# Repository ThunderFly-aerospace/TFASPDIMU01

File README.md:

# TFASPDIMU01 - sdp3x differental pressure sensor and IMU 9-axis unit

ThunderFly TFASPDIMU01 is SPI/I2C sensor board equipped with a differential pressure sensor (Senserion [SDP3x](https://www.sensirion.com/sdp3x/)) and 9-axis motion tracking sensor ([ICM-20948](https://invensense.tdk.com/products/motion-tracking/9-axis/icm-20948/)). Board is equipped with 7pin JST-GH connector. The sensor board is designed for multiple uses. It can be used as a self-adjusting anemometer [WINDGAUGE03](https://github.com/mlab-modules/WINDGAUGE03) or as an airspeed sensor for UAVs with optional function as the external magnetometer.

TFASPDIMU is commercially available from [ThunderFly s.r.o.](https://www.thunderfly.cz/), write an email to info@thunderfly.cz or shop at [Tindie store](https://www.tindie.com/stores/thunderfly/).

## Specification
 * Type: Differential and 9-axis motion sensor board
 * Mass: 3 g
 * Size: 36 x 14 mm
 * Power: +5 V
 * Connection: 7pin JST-GH connector, custom pinout

**SDP3x**
 * Range: +/- 125/500 Pa (depending on exact sensor type)
 * Excellent accuracy and repeatability, even below one Pascal
 * No zero-point offset, no temperature drift
 * Calibrated and temperature compensated
 * Fast sampling time of 2kHz at 16 bit resolution
 * I2C address: 0x21 (d33)

 **ICM-20948**
 * 3-axis gyroscope, 3-axis accelerometer, 3-axis compass (magnetometer)
 * Onboard Digital Motion Processor (DMP)
 * On-Chip 16-bit ADCs and Programmable Filters
 * 7 MHz SPI or 400 kHz Fast Mode I²C
 * Digital temperature sensor
 * Default I2C address: 0x68 (0d104), can be changed to 0x69 (0d105) by moving the resistor R2->R1. 

## Example of uses

### WINDGUAGE01

Ground control station anemometer [WINDGAUGE03](https://github.com/mlab-modules/WINDGAUGE03)

### TFSLOT01 - UAV airspeed sensor

Our [TFSLOT](https://github.com/ThunderFly-aerospace/TFSLOT01) senzor is an airspeed sensor for use mainly on UAV. Due to 3D printed case it is possible to optimalize part according to the location of sensor on UAV and tune their characteristics. First use of this sensor was on our autogyro [TF-G2](https://github.com/ThunderFly-aerospace/TF-G2/).

More details about this solution is available in the repository [TFSLOT01](https://github.com/ThunderFly-aerospace/TFSLOT01).

### TFPIPE01 - UAV airspeed sensor

Symmetric variant of TFSLOT sensor for different mounting options [TFPIPE01](https://github.com/ThunderFly-aerospace/TFPIPE01).

### TFVENTUFO - omnidirectional anemometer
This anemometer should also based on venturi effect. Thanks to an clever design, it will measure the wind speed from all directions (without knowing the direction).

### Angle of Attack sensor

In case of mounting on rotation slip-ring bearing the sensor could sense air [AoA of the vehicle](https://en.wikipedia.org/wiki/Angle_of_attack). Due to ability to turn in direction of airflow. The turnig direction could be sensed differentialy to position of aircraft by IMU embedded in the TFASPDIMU01 sensor. 

## Hardware

### Eletronic schema

Full schema is avialible in [PDF](/hw/sch_pcb/TFASPDIMU01.pdf)

### Hardware layout

** IMG - technical draft **

### Pinout
|Pin #| I2C | SPI  |
| --- |:---:|:----:|
| 1   | +5V | +5V  |
| 2   | SCL | SCK  |
| 3   | --  | MISO |
| 4   | SDA | MOSI |
| 5   | --  | CS   |
| 6   | INT | INT  |
| 7   | GND | GND  |
> Due to the possible wider use of the sensor, a standard pixhawk pinout is not used.

#### PixHawk autopilot cable

To increase the transmission quality, it is recommended to create pairs SDA,GND and SCL,+5V on the cable (as shown in image)

| TFASPDIMU01 Pin | Sigal | Pixhawk | Color |
| ---------------:|:-----:|:-------:|-------|
|   1             | +5V   |  1      | Red   |
|   2             | SCL   |  2      | Yellow|
|   4             | SDA   |  3      | Green |
|   7             | GND   |  4      | Black |
> Pixhawk pinout is listed according to the [Pixhawk connector standard](https://github.com/pixhawk/Pixhawk-Standards/blob/master/DS-009%20Pixhawk%20Connector%20Standard.pdf).

## Usage

### Python
For reading data from the sensor, we have prepared a python script in PyMLAB library that uses the pySMBus to readout data. It can be used directly from a computer with a corresponding converter (for example MLAB [USBI2C01A](https://wiki.mlab.cz/doku.php?id=cs:usbi2c)) or with one-board computers (Odroid, raspberry and similar) that have own smbus output.

#### Calibration vertification
Calibration can be verified by mounting of an anemometer to car roof and comparing it to speed obtained from GPS (gpsd). This needs to be done in windless weather.

### PX4
> We are now working on implementation of driver into PX4 stack.

Main usage of this sensor is as airspeed sensor. It can be also used as an external magnetometer and thermometer.

### Ardupilot
We are currently unable to implement the sensor in the Ardupilot flight stack. However, we will be happy to provide assistance with implementation. You can [contact us](https://www.thunderfly.cz/contact-us.html)

#### configuration
*TODO*

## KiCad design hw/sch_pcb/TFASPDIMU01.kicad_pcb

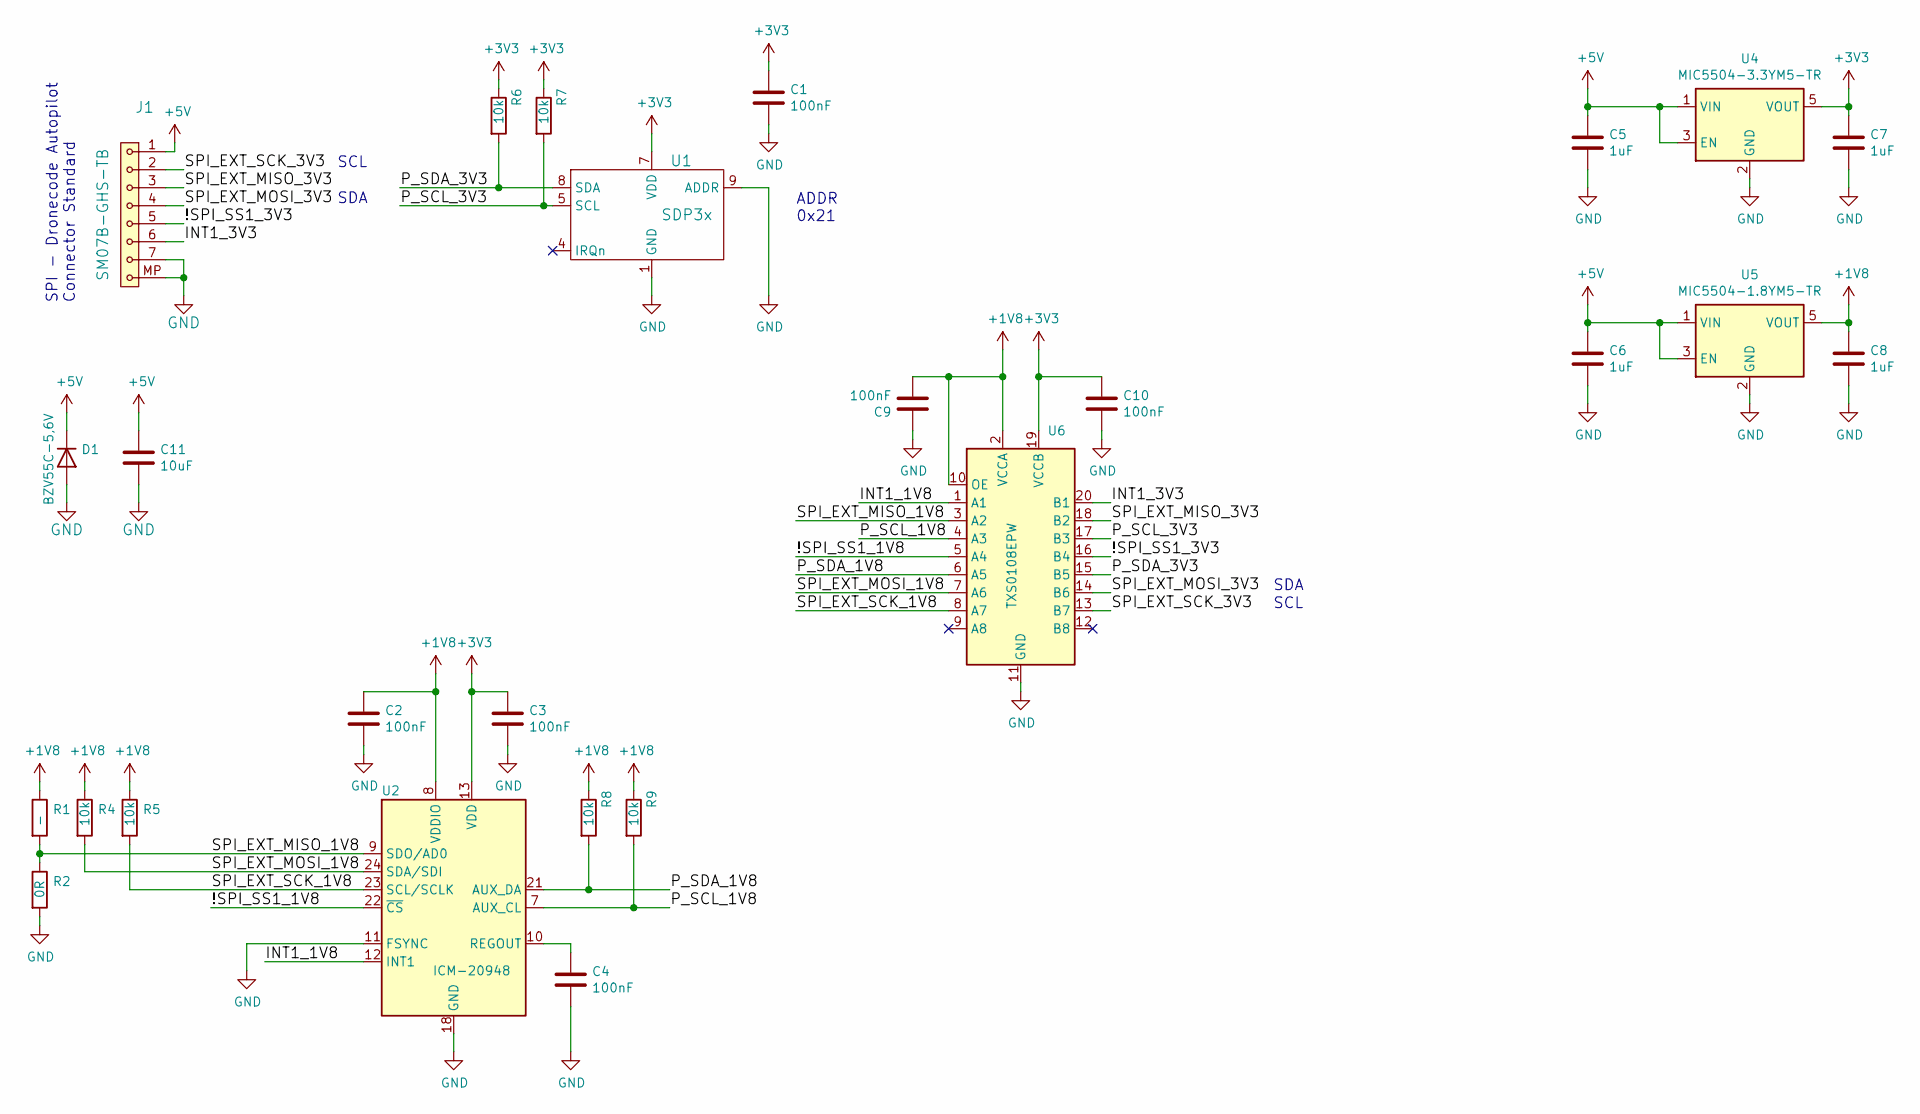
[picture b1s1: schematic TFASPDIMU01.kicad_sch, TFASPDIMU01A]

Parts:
C1, C2, C3, C4, C9, C10: 100nF; SMD-0603
C5, C6, C7, C8: 1uF; SMD-0603
C11: 10uF; SMD-0805
D1: BZV55C-5,6V; D_MiniMELF
J1: SM07B-GHS-TB; JST_GH_SM07B-GHS-TB_1x07-1MP_P1.25mm_Horizontal
R1: -; SMD-0603
R2: 0R; SMD-0603
R4, R5, R6, R7, R8, R9: 10k; SMD-0603
U1: SDP3x
U2: ICM-20948; InvenSense_QFN-24_3x3mm_P0.4mm
U4: MIC5504-3.3YM5-TR; SOT-23-5
U5: MIC5504-1.8YM5-TR; SOT-23-5
U6: TXS0108EPW; TSSOP-20_4.4x6.5mm_P0.65mm

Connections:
+1V8: C2.1, C8.1, C9.2, R1.1, R4.1, R5.1, R8.1, R9.1, U2.8 (VDDIO), U5.5 (VOUT), U6.2 (VCCA), U6.10 (OE)
+3V3: C1.1, C3.1, C7.1, C10.1, R6.1, R7.1, U1.7 (VDD), U2.13 (VDD), U4.5 (VOUT), U6.19 (VCCB)
+5V: C5.1, C6.1, C11.1, D1.1 (K), J1.1, U4.1 (VIN), U4.3 (EN), U5.1 (VIN), U5.3 (EN)
/!SPI_SS1_1V8: U2.22 (~CS), U6.5 (A4)
/!SPI_SS1_3V3: J1.5, U6.16 (B4)
/INT1_1V8: U2.12 (INT1), U6.1 (A1)
/INT1_3V3: J1.6, U6.20 (B1)
/P_SCL_1V8: R9.2, U2.7 (AUX_CL), U6.4 (A3)
/P_SCL_3V3: R7.2, U1.5 (SCL), U6.17 (B3)
/P_SDA_1V8: R8.2, U2.21 (AUX_DA), U6.6 (A5)
/P_SDA_3V3: R6.2, U1.8 (SDA), U6.15 (B5)
/SPI_EXT_MISO_1V8: R1.2, R2.1, U2.9 (SDO/AD0), U6.3 (A2)
/SPI_EXT_MISO_3V3: J1.3, U6.18 (B2)
/SPI_EXT_MOSI_1V8: R4.2, U2.24 (SDA/SDI), U6.7 (A6)
/SPI_EXT_MOSI_3V3: J1.4, U6.14 (B6)
/SPI_EXT_SCK_1V8: R5.2, U2.23 (SCL/SCLK), U6.8 (A7)
/SPI_EXT_SCK_3V3: J1.2, U6.13 (B7)
GND: C1.2, C2.2, C3.2, C4.2, C5.2, C6.2, C7.2, C8.2, C9.1, C10.2, C11.2, D1.2 (A), J1.7, J1.MP, R2.2, U1.1 (GND), U1.2 (GND), U1.3 (GND), U1.6 (GND), U1.9 (ADDR), U1.10 (GND), U1.11 (GND), U1.17 (GND), U1.18 (GND), U2.11 (FSYNC), U2.18 (GND), U2.20 (GND), U4.2 (GND), U5.2 (GND), U6.11 (GND)
unnamed: C4.1, U2.10 (REGOUT)

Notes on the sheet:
SDA
SCL
ADDR 0x21
SPI - Dronecode Autopilot Connector Standard

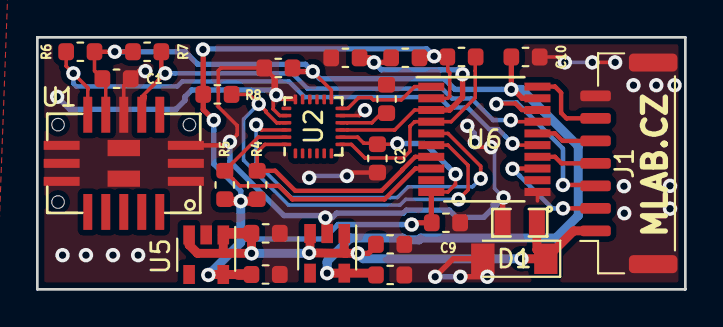
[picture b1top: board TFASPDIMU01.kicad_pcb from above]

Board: 2 copper layers, 36.0 x 14.0 mm, 26 parts (0 on the bottom side), 19 nets.

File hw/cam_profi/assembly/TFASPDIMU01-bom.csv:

Component,Description,Part,References,Value,Footprint,Quantity Per PCB,Datasheet,ust_id
1,Unpolarized capacitor,C,C1C2C3C4C9C10,100nF,SMD-0603,6,~,5c70984712875079b91f8b4c
2,Unpolarized capacitor,C,C5C6C7C8,1uF,SMD-0603,4,~,5c70984712875079b91f8b50
3,Unpolarized capacitor,C,C11,10uF,SMD-0805,1,~,5c70984812875079b91f8bbd
4,Diode,D,D1,"BZV55C-5,6V",D_MiniMELF,1,~,5c70984512875079b91f88b1
5,1x08 2.54 mm pitch header,SM07B-GHS-TB,J1,SM07B-GHS-TB,JST_GH_SM07B-GHS-TB_1x07-1MP_P1.25mm_Horizontal,1,,5c7250081287500b4e112e78
6,Resistor,R,R2,0R,SMD-0603,1,~,5c70984512875079b91f896b
7,Resistor,R,R4R5R6R7R8R9,10k,SMD-0603,6,~,5c70984612875079b91f899f
8,Resistor,R,R1,-,SMD-0603,1,~,
9,"InvenSense 9-Axis Motion Sensor, Accelerometer, Gyroscope, Compass, I2C/SPI, QFN-24",ICM-20948,U2,ICM-20948,InvenSense_QFN-24_3x3mm_P0.4mm,1,http://www.invensense.com/wp-content/uploads/2016/06/DS-0001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,5c725a431287500b4e112ef5
10,"300mA Low-dropout Voltage Regulator, Vout 1.8V, Vin up to 5.5V, SOT-23",MIC5504-1.8YM5,U5,MIC5504-1.8YM5-TR,SOT-23-5,1,http://ww1.microchip.com/downloads/en/DeviceDoc/MIC550X.pdf,5c7256781287500b4e112eba
11,"300mA Low-dropout Voltage Regulator, Vout 3.3V, Vin up to 5.5V, SOT-23",MIC5504-3.3YM5,U4,MIC5504-3.3YM5-TR,SOT-23-5,1,http://ww1.microchip.com/downloads/en/DeviceDoc/MIC550X.pdf,5c7255e81287500b4e112ea2
12,,SDP3x,U1,SDP3x,SDP3x,1,,5c70984812875079b91f8bd0
13,"Bidirectional  level-shifting voltage translator, TSSOP-20",TXS0108EPW,U6,TXS0108EPW,TSSOP-20_4.4x6.5mm_P0.65mm,1,www.ti.com/lit/ds/symlink/txs0108e.pdf,5c7258471287500b4e112edd

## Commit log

2019-02-07 edit
2019-04-01 Dimensions added to PCB layout.
2019-04-01 Dimensions export.
2020-01-25 edit description
2020-02-13 Rouding of PCB elevation to allow cable winding under the cover.
2020-04-01 Adding PCB cam files.
2020-10-29 readme of PCB
2020-10-29 Create LICENSE
2020-10-29 zmena struktury
2020-10-29 odebrani vyrobnich dat
2020-10-29 docs
2020-10-29 pcb_img
2020-10-30 pridani examplu
2020-10-30 Edit PCB for 3D model
2020-10-30 Edit 3D image
2020-10-30 Edit image
2020-10-30 Automation
2020-10-30 Edit schema
2020-10-31 logger
2020-11-02 Uprava logovaciho skriptu
2020-11-11 Add color description of cable in the photo
2020-11-16 renamed to gpsd logger because the main advantage of script is ability to log gpsd data.
2021-01-14 Documentation improvement.
2021-02-25 Schematics update.
2021-04-05 Update title block.
2021-06-08 Improve I2C marking in schematics.
2021-06-09 Fix wrong default address definition.
2022-01-29 Add link to AoA sensing.
2024-06-17 Update the project to KiCAD7.
2024-06-17 Update actions products
2024-07-17 Update workflow files
2026-02-22 Cleanup and update project to KiCADv9.
2026-02-22 Automatic update of KiCAD outputs

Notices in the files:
hw/sch_pcb/TFASPDIMU01.kicad_sch:
GPL 3.0
